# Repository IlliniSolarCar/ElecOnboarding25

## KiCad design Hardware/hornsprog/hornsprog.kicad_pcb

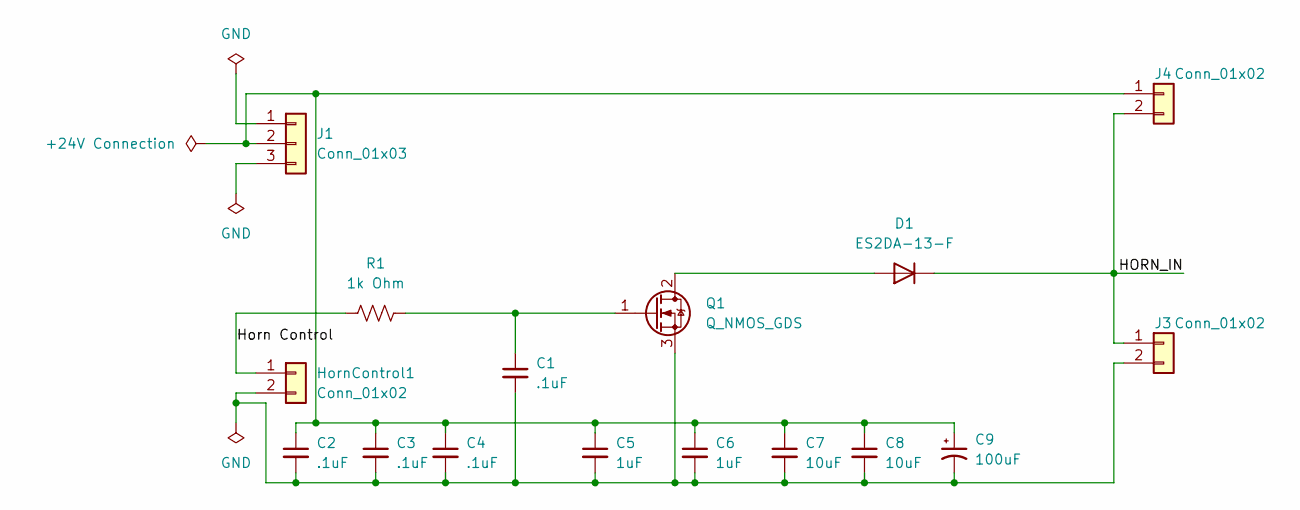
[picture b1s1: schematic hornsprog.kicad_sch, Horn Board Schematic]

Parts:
C1, C2, C3, C4: .1uF; C_0603_1608Metric
C5, C6: 1uF; C_0603_1608Metric
C7, C8: 10uF; C_0603_1608Metric
C9: 100uF; C_0603_1608Metric
D1: ES2DA-13-F; D_DO-41_SOD81_P10.16mm_Horizontal
HornControl1: Conn_01x02; Molex_KK-254_AE-6410-02A_1x02_P2.54mm_Vertical
J1: Conn_01x03; Molex_KK-254_AE-6410-03A_1x03_P2.54mm_Vertical
J3, J4: Conn_01x02; Molex_KK-254_AE-6410-02A_1x02_P2.54mm_Vertical
Q1: Q_NMOS_GDS; TO-252-2
R1: 1k Ohm; R_0603_1608Metric

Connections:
/HORN_IN: D1.1 (K), J3.1, J4.2
/Horn Control: HornControl1.1, R1.1
unnamed: D1.2 (A), Q1.2 (D)
unnamed: C1.2, C2.2, C3.2, C4.2, C5.2, C6.2, C7.2, C8.2, C9.2, HornControl1.2, J3.2, Q1.3 (S)
unnamed: C2.1, C3.1, C4.1, C5.1, C6.1, C7.1, C8.1, C9.1, J1.2, J4.1
unnamed: C1.1, Q1.1 (G), R1.2

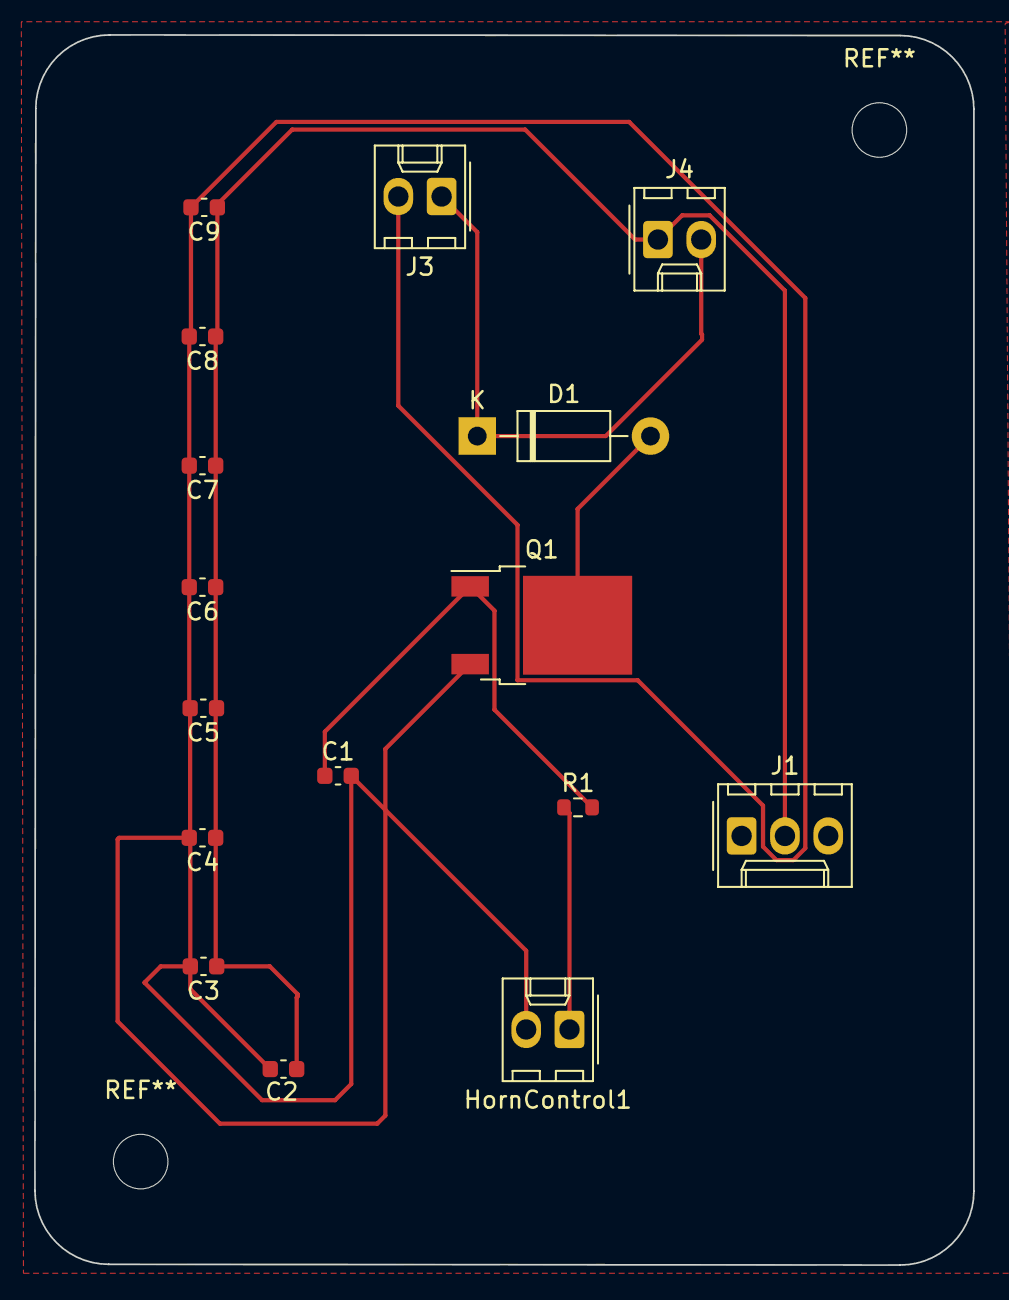
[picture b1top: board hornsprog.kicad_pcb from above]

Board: 2 copper layers, 55.1 x 72.1 mm, 16 parts (0 on the bottom side), 6 nets.

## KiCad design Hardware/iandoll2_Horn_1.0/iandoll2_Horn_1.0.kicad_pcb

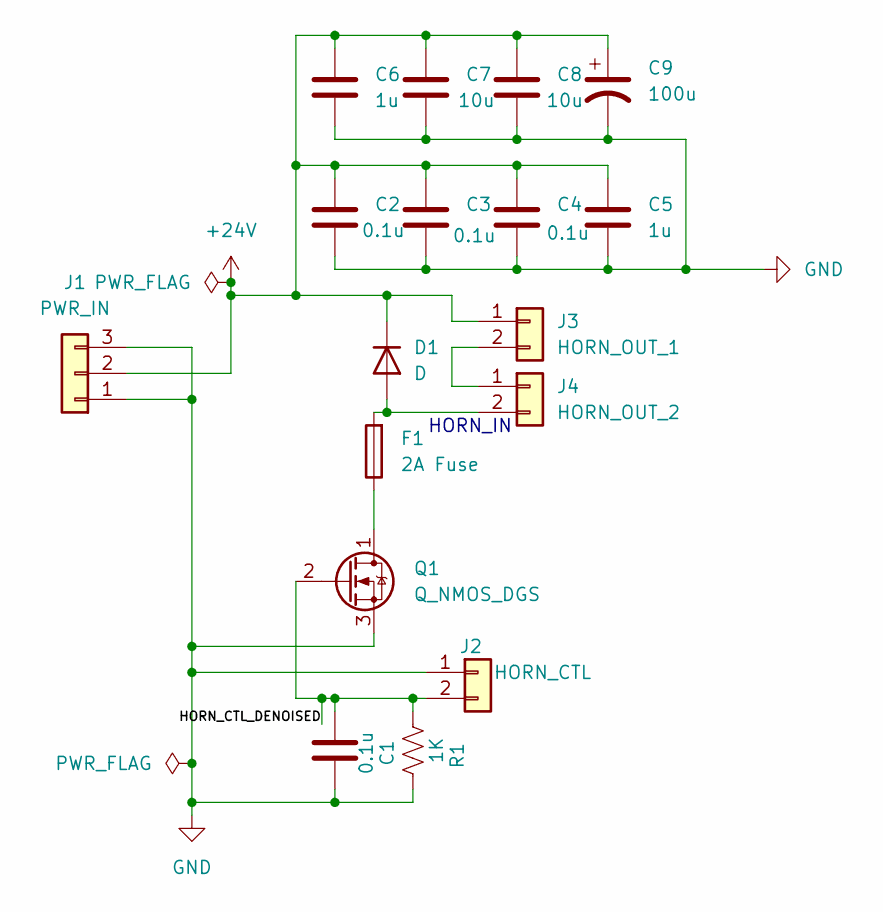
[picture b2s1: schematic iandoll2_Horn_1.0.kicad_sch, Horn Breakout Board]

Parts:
C1, C2, C3, C4: 0.1u; C_0603_1608Metric_Pad1.08x0.95mm_HandSolder
C5, C6: 1u; C_0603_1608Metric_Pad1.08x0.95mm_HandSolder
C7, C8: 10u; C_0603_1608Metric_Pad1.08x0.95mm_HandSolder
C9: 100u; CP_Radial_Tantal_D7.0mm_P2.50mm
D1: D; D_0603_1608Metric_Pad1.05x0.95mm_HandSolder; MPN ES2DA-13-F
F1: 2A Fuse; Fuse_0603_1608Metric_Pad1.05x0.95mm_HandSolder
J1: PWR_IN; Molex_Micro-Fit_3.0_43650-0300_1x03_P3.00mm_Horizontal; MPN 436500300
J2: HORN_CTL; Molex_Micro-Fit_3.0_43650-0200_1x02_P3.00mm_Horizontal; MPN 436500200
J3: HORN_OUT_1; Molex_Micro-Fit_3.0_43650-0200_1x02_P3.00mm_Horizontal; MPN 436500200
J4: HORN_OUT_2; Molex_Micro-Fit_3.0_43650-0200_1x02_P3.00mm_Horizontal; MPN 436500200
Q1: Q_NMOS_DGS; TO-252-2; MPN IRFR010PBF
R1: 1K; R_0603_1608Metric_Pad0.98x0.95mm_HandSolder

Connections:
+24V: C2.1, C3.1, C4.1, C5.1, C6.1, C7.1, C8.1, C9.1, D1.1 (K), J1.2, J3.1
/HORN_CTL_DENOISED: C1.2, J2.2, Q1.2 (G), R1.2
GND: C1.1, C2.2, C3.2, C4.2, C5.2, C6.2, C7.2, C8.2, C9.2, J1.1, J1.3, J2.1, Q1.3 (S), R1.1
unnamed: D1.2 (A), F1.2, J4.2
unnamed: J3.2, J4.1
unnamed: F1.1, Q1.1 (D)

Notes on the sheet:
HORN_IN

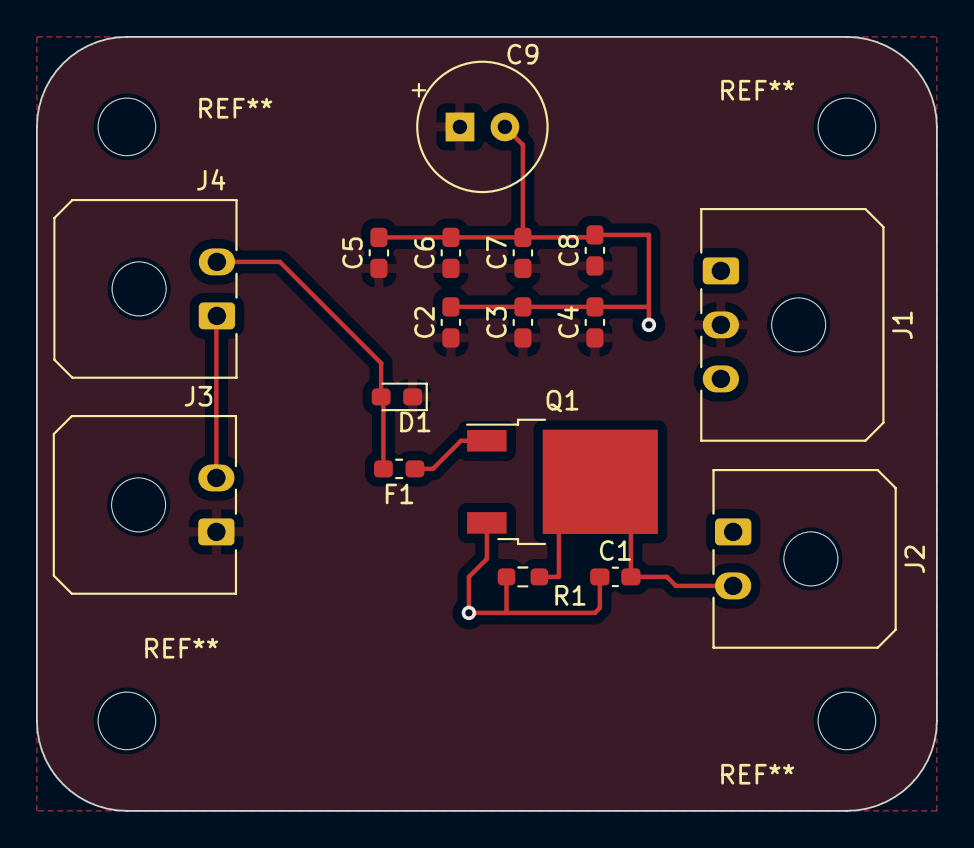
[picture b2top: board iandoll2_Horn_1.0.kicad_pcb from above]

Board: 2 copper layers, 50.0 x 43.0 mm, 17 parts (0 on the bottom side), 6 nets.

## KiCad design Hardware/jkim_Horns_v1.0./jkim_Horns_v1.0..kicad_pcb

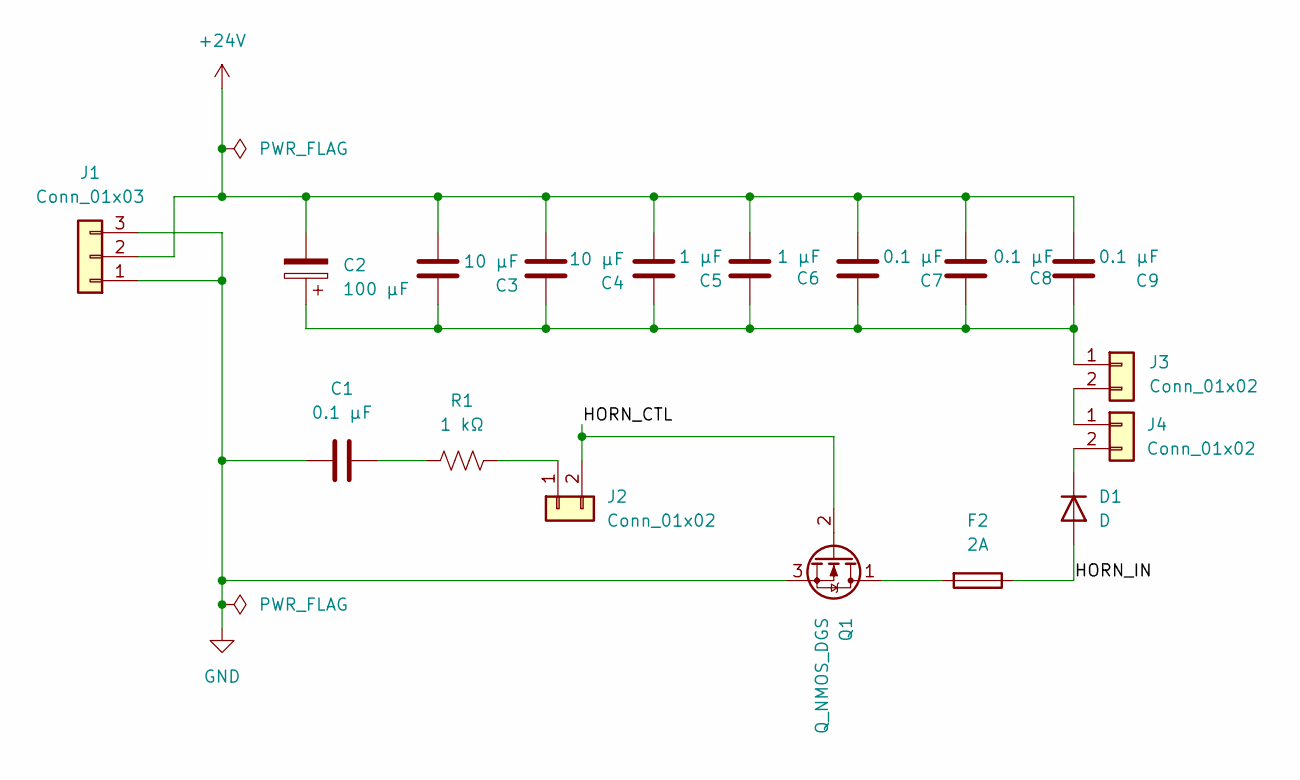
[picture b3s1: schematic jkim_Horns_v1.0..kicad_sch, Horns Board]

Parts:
C1, C7, C8, C9: 0.1 µF; C_0603_1608Metric
C2: 100 µF; C_0603_1608Metric
C3, C4: 10 µF; C_0603_1608Metric
C5, C6: 1 µF; C_0603_1608Metric
D1: D; D_0603_1608Metric_Pad1.05x0.95mm_HandSolder
F2: 2A; D_SOD-123F
J1: Conn_01x03; Molex_KK-254_AE-6410-03A_1x03_P2.54mm_Vertical
J2, J3, J4: Conn_01x02; Molex_KK-254_AE-6410-02A_1x02_P2.54mm_Vertical
Q1: Q_NMOS_DGS; TO-252-2
R1: 1 kΩ; R_0603_1608Metric_Pad0.98x0.95mm_HandSolder

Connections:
+24V: C2.2, C3.2, C4.2, C5.2, C6.2, C7.2, C8.2, C9.2, J1.2
/HORN_CTL: J2.2, Q1.2 (G)
/HORN_IN: D1.2 (A), F2.1
GND: C1.2, J1.1, J1.3, Q1.3 (S)
unnamed: C1.1, R1.2
unnamed: D1.1 (K), J4.2
unnamed: J2.1, R1.1
unnamed: C2.1, C3.1, C4.1, C5.1, C6.1, C7.1, C8.1, C9.1, J3.1
unnamed: J3.2, J4.1
unnamed: F2.2, Q1.1 (D)

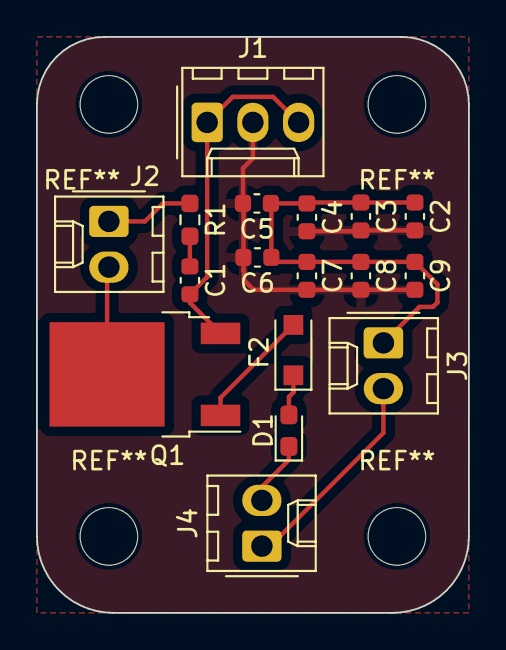
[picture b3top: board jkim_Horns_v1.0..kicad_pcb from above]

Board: 2 copper layers, 24.0 x 32.0 mm, 17 parts (0 on the bottom side), 10 nets.

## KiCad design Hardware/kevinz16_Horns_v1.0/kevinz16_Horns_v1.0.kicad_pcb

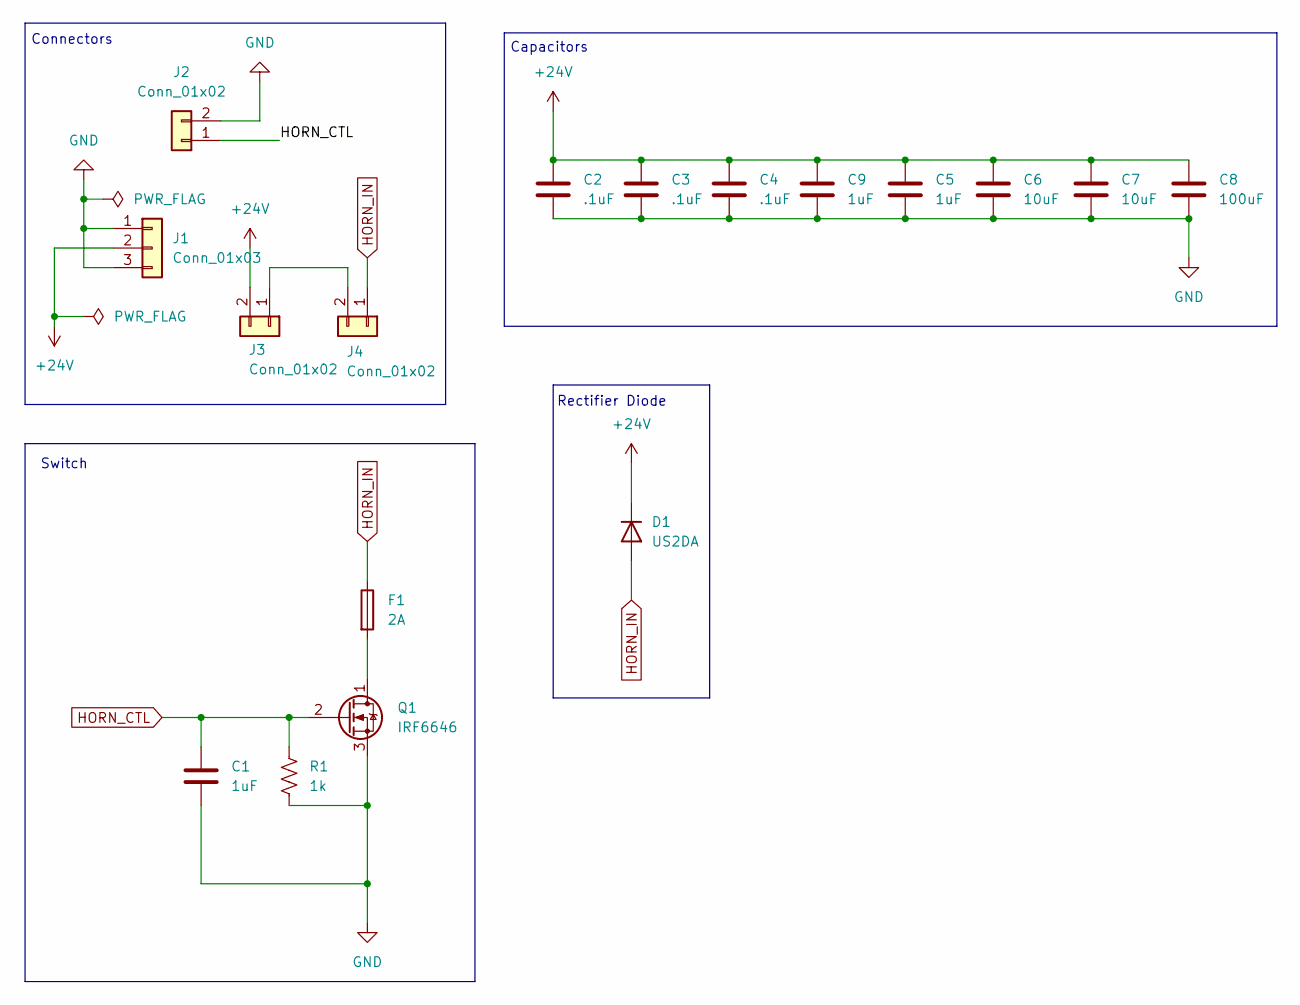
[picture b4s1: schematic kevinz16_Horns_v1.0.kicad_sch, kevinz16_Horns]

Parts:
C1, C5, C9: 1uF; C_0603_1608Metric_Pad1.08x0.95mm_HandSolder
C2, C3, C4: .1uF; C_0603_1608Metric_Pad1.08x0.95mm_HandSolder
C6, C7: 10uF; C_0603_1608Metric_Pad1.08x0.95mm_HandSolder
C8: 100uF; C_0603_1608Metric_Pad1.08x0.95mm_HandSolder
D1: US2DA; D_SMA
F1: 2A; Fuse_0603_1608Metric_Pad1.05x0.95mm_HandSolder
J1: Conn_01x03; Molex_KK-254_AE-6410-03A_1x03_P2.54mm_Vertical
J2, J3, J4: Conn_01x02; Molex_KK-254_AE-6410-02A_1x02_P2.54mm_Vertical
Q1: IRF6646; DirectFET_MN
R1: 1k; R_0603_1608Metric_Pad0.98x0.95mm_HandSolder

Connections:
+24V: C2.1, C3.1, C4.1, C5.1, C6.1, C7.1, C8.1, C9.1, D1.1 (K), J1.2, J3.2
GND: C1.2, C2.2, C3.2, C4.2, C5.2, C6.2, C7.2, C8.2, C9.2, J1.1, J1.3, J2.2, Q1.3 (S), R1.2
HORN_CTL: C1.1, J2.1, Q1.2 (G), R1.1
HORN_IN: D1.2 (A), F1.1, J4.1
unnamed: J3.1, J4.2
unnamed: F1.2, Q1.1 (D)

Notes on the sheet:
Connectors
Rectifier Diode
Switch
Capacitors

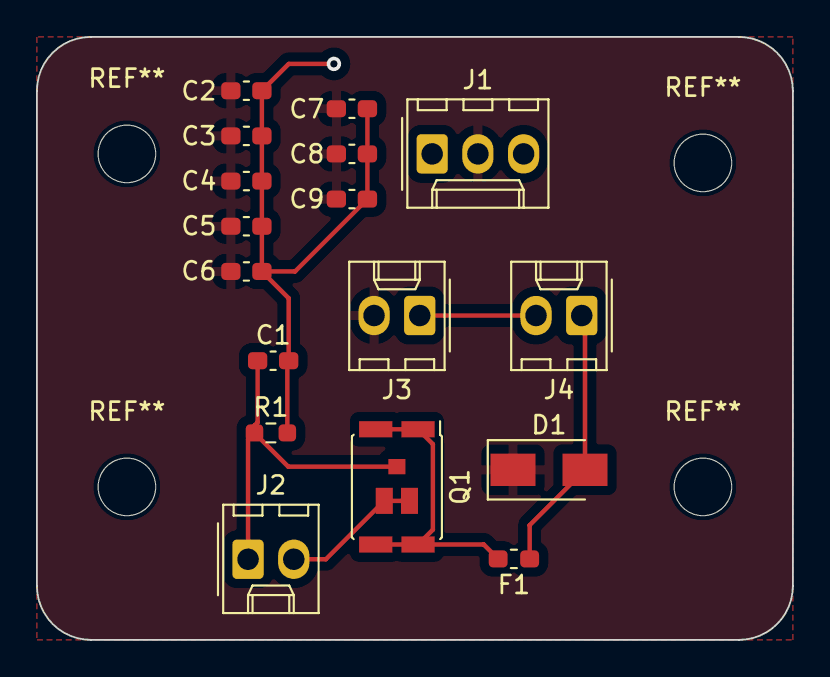
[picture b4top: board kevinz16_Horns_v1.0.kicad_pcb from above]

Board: 2 copper layers, 42.0 x 33.5 mm, 17 parts (0 on the bottom side), 6 nets.

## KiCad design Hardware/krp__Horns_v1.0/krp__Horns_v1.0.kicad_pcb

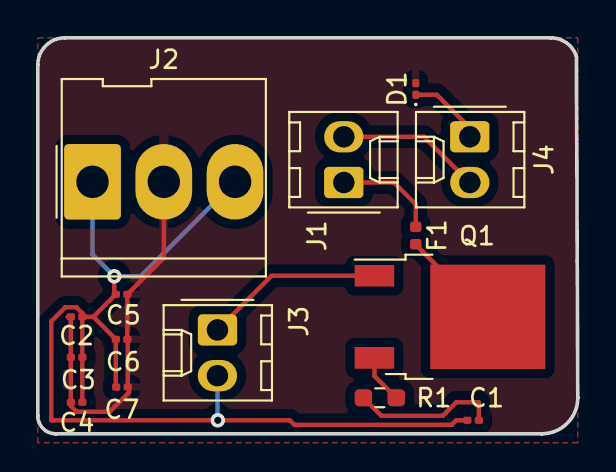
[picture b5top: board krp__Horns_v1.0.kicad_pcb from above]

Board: 2 copper layers, 30.0 x 22.0 mm, 15 parts (0 on the bottom side), 9 nets.

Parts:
C1, C2, C3, C4: 0.1uF; C_0201_0603Metric
C5, C6: 1uF; C_0201_0603Metric
C7: 100uF; C_0201_0603Metric
D1: D; D_0201_0603Metric
F1: 2A; Fuse_0402_1005Metric
J1, J4: Conn_01x02 (Horn Out); Molex_KK-254_AE-6410-02A_1x02_P2.54mm_Vertical
J2: Conn_01x03 (Power); Molex_KK-396_5273-03A_1x03_P3.96mm_Vertical
J3: Conn_01x02 (Horn Control); Molex_KK-254_AE-6410-02A_1x02_P2.54mm_Vertical
Q1: Q_NMOS_GDS; TO-252-2
R1: 1k; R_0603_1608Metric_Pad0.98x0.95mm_HandSolder

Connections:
+24V: C2.2, C3.2, C4.1, C5.2, C6.2, C7.2, D1.2 (A), J2.2
GND: C1.2, C2.1, C3.1, C4.2, C5.1, C6.1, C7.1, J2.1, J2.3, J3.2
Net Label: J3.1, Q1.1 (G)
unnamed: C1.1, R1.2
unnamed: D1.1 (K), J4.1
unnamed: F1.1, J1.1
unnamed: J1.2, J4.2
unnamed: F1.2, Q1.2 (D)
unnamed: Q1.3 (S), R1.1

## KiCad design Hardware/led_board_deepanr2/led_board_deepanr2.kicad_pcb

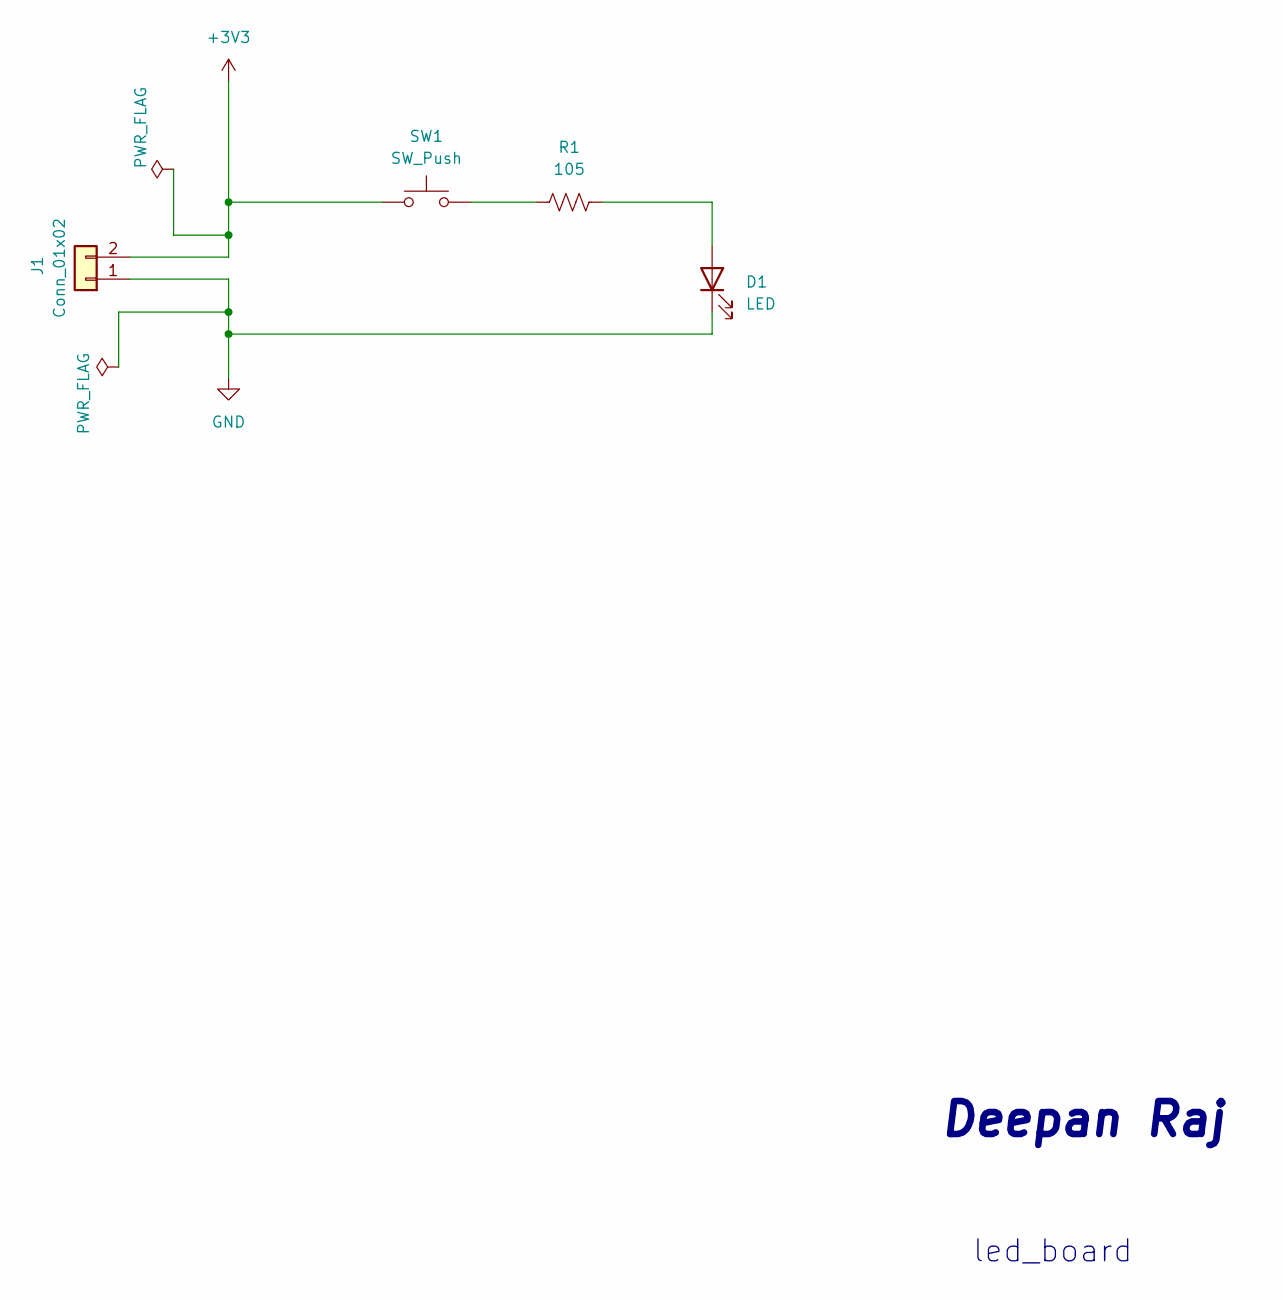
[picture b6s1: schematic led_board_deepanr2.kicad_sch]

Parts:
D1: LED; LED_D10.0mm-3
J1: Conn_01x02; Molex_KK-254_AE-6410-02A_1x02_P2.54mm_Vertical
R1: 105; R_0603_1608Metric_Pad0.98x0.95mm_HandSolder
SW1: SW_Push; SW_DIP_SPSTx01_Slide_6.7x4.1mm_W8.61mm_P2.54mm_LowProfile

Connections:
+3V3: J1.2, SW1.1
GND: D1.1 (K), J1.1
unnamed: D1.2 (A), R1.2
unnamed: R1.1, SW1.2

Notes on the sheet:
Deepan Raj
led_board

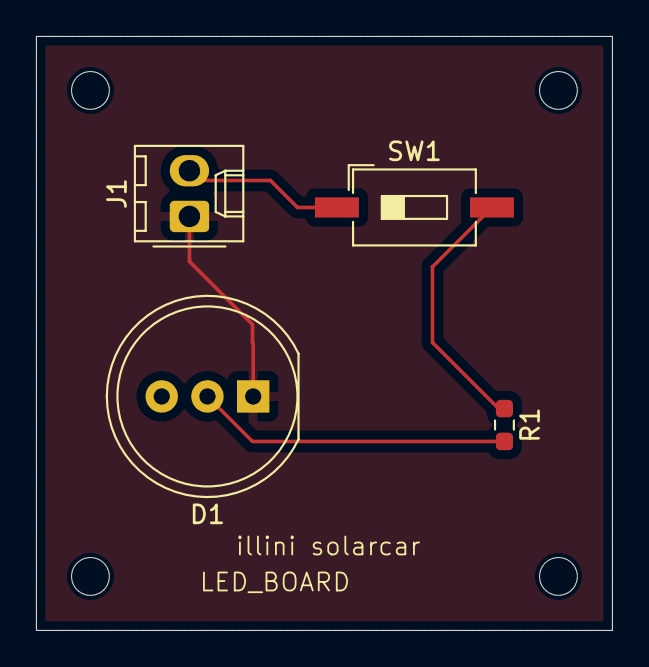
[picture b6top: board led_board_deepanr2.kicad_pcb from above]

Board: 2 copper layers, 32.0 x 33.0 mm, 4 parts (0 on the bottom side), 4 nets.

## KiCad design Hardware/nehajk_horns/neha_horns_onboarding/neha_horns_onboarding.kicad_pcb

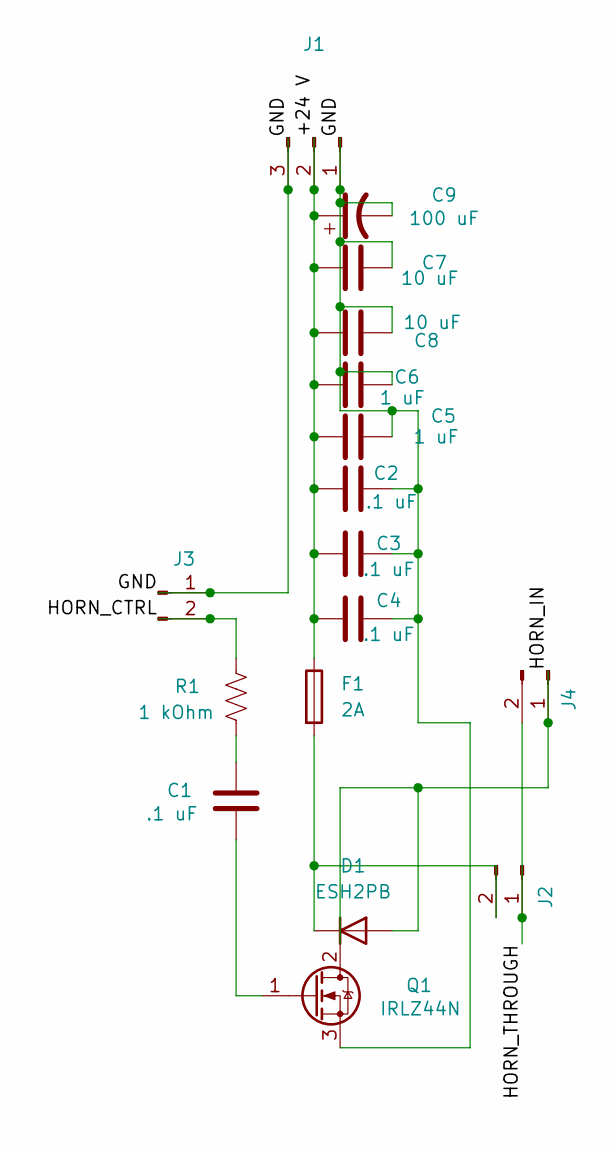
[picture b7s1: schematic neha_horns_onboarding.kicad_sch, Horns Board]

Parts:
C1, C2, C3, C4: .1 uF; C_0603_1608Metric_Pad1.08x0.95mm_HandSolder
C5, C6: 1 uF; C_0603_1608Metric_Pad1.08x0.95mm_HandSolder
C7, C8: 10 uF; C_0603_1608Metric_Pad1.08x0.95mm_HandSolder
C9: 100 uF; C_0603_1608Metric_Pad1.08x0.95mm_HandSolder
D1: ESH2PB; D_0603_1608Metric_Pad1.05x0.95mm_HandSolder
F1: 2A; Fuse_0603_1608Metric_Pad1.05x0.95mm_HandSolder
J1: Conn_01x02_Pin; Molex_KK-254_AE-6410-03A_1x03_P2.54mm_Vertical
J2, J3, J4: Conn_01x02_Pin; Molex_KK-254_AE-6410-02A_1x02_P2.54mm_Vertical; MPN Molex 22-01-3027
Q1: IRLZ44N; TO-220-3_Vertical
R1: 1 kOhm; R_0603_1608Metric_Pad0.98x0.95mm_HandSolder

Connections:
/+24 V: C2.1, C3.1, C4.1, C5.1, C6.1, C7.2, C8.2, C9.1, F1.1, J1.2
/GND: C2.2, C3.2, C4.2, C5.2, C6.2, C7.1, C8.1, C9.2, J1.1, J1.3, J3.1, Q1.3 (S)
/HORN_CTRL: J3.2, R1.1
/HORN_IN: D1.2 (A), J4.1, Q1.2 (D)
/HORN_THROUGH: J2.1, J4.2
unnamed: C1.1, R1.2
unnamed: D1.1 (K), F1.2, J2.2
unnamed: C1.2, Q1.1 (G)

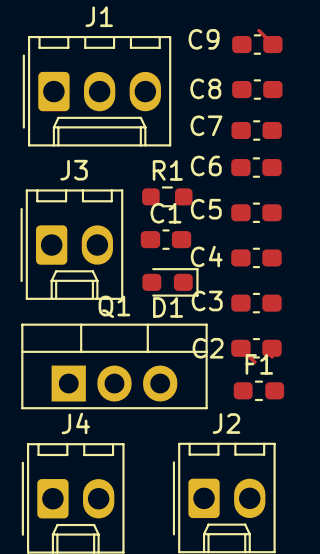
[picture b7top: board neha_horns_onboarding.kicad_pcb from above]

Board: 2 copper layers, 17 parts (0 on the bottom side), 8 nets.

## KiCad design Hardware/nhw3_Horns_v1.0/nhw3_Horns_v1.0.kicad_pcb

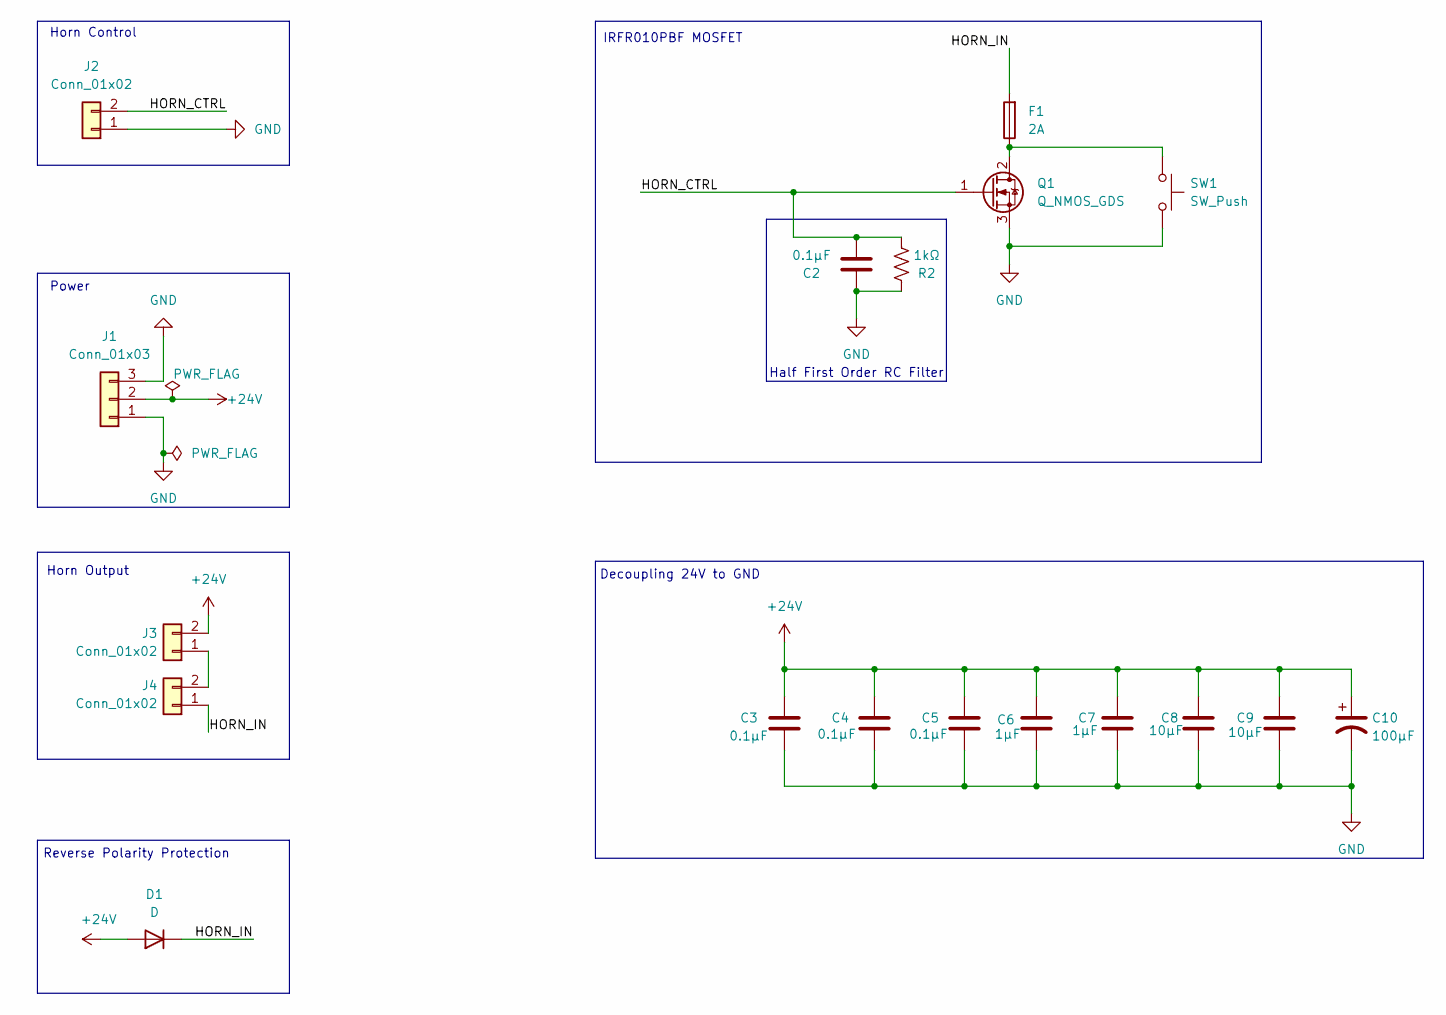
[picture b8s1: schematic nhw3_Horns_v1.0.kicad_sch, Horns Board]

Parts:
C2, C3, C4, C5: 0.1μF; C_0603_1608Metric_Pad1.08x0.95mm_HandSolder
C6, C7: 1μF; C_0603_1608Metric_Pad1.08x0.95mm_HandSolder
C8, C9: 10μF; C_0603_1608Metric_Pad1.08x0.95mm_HandSolder
C10: 100μF; C_0603_1608Metric_Pad1.08x0.95mm_HandSolder
D1: D; D_0603_1608Metric_Pad1.05x0.95mm_HandSolder; MPN ES2DA-13-F
F1: 2A; Fuse_0603_1608Metric_Pad1.05x0.95mm_HandSolder
J1: Conn_01x03; Molex_Micro-Fit_3.0_43650-0300_1x03_P3.00mm_Horizontal; MPN 0022272031
J2, J3, J4: Conn_01x02; Molex_Micro-Fit_3.0_43650-0200_1x02_P3.00mm_Horizontal; MPN 022272021
Q1: Q_NMOS_GDS; TO-252-2; MPN IRFR010PBF
R2: 1kΩ; R_0603_1608Metric_Pad0.98x0.95mm_HandSolder
SW1: SW_Push; SW_Push_1P1T_NO_CK_KMR2

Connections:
+24V: C3.1, C4.1, C5.1, C6.1, C7.1, C8.1, C9.1, C10.1, D1.2 (A), J1.2, J3.2
/HORN_CTRL: C2.1, J2.2, Q1.1 (G), R2.1; also elsewhere on the board
/HORN_IN: D1.1 (K), F1.2, J4.1
GND: C2.2, C3.2, C4.2, C5.2, C6.2, C7.2, C8.2, C9.2, C10.2, J1.1, J1.3, J2.1, Q1.3 (S), R2.2, SW1.2
unnamed: J3.1, J4.2
unnamed: F1.1, Q1.2 (D), SW1.1

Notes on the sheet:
Power
IRFR010PBF MOSFET
Horn Control
Decoupling 24V to GND
Reverse Polarity Protection
Half First Order RC Filter
Horn Output

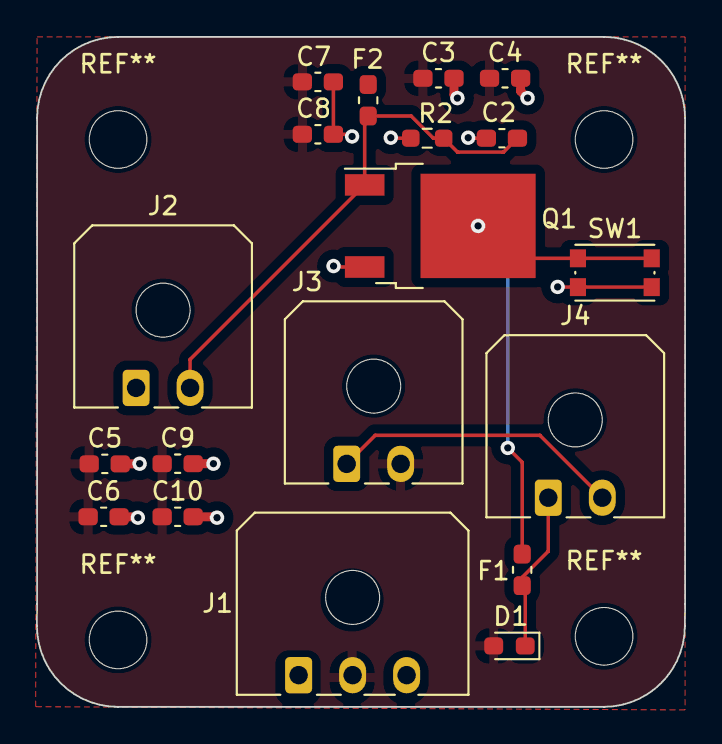
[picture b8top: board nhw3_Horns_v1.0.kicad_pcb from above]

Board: 2 copper layers, 36.0 x 37.2 mm, 19 parts (0 on the bottom side), 6 nets.

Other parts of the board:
F2: 2A; Fuse_0603_1608Metric_Pad1.05x0.95mm_HandSolder

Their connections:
/HORN_CTRL: F2.2; also elsewhere on the board
